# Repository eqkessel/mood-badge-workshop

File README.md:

# mood-badge-workshop
Repository to house my work for making a mood badge for the Spring 2021 Intro to Electronics Pro Milestones Workshop offered through the Purdue Office of Professional Practice.

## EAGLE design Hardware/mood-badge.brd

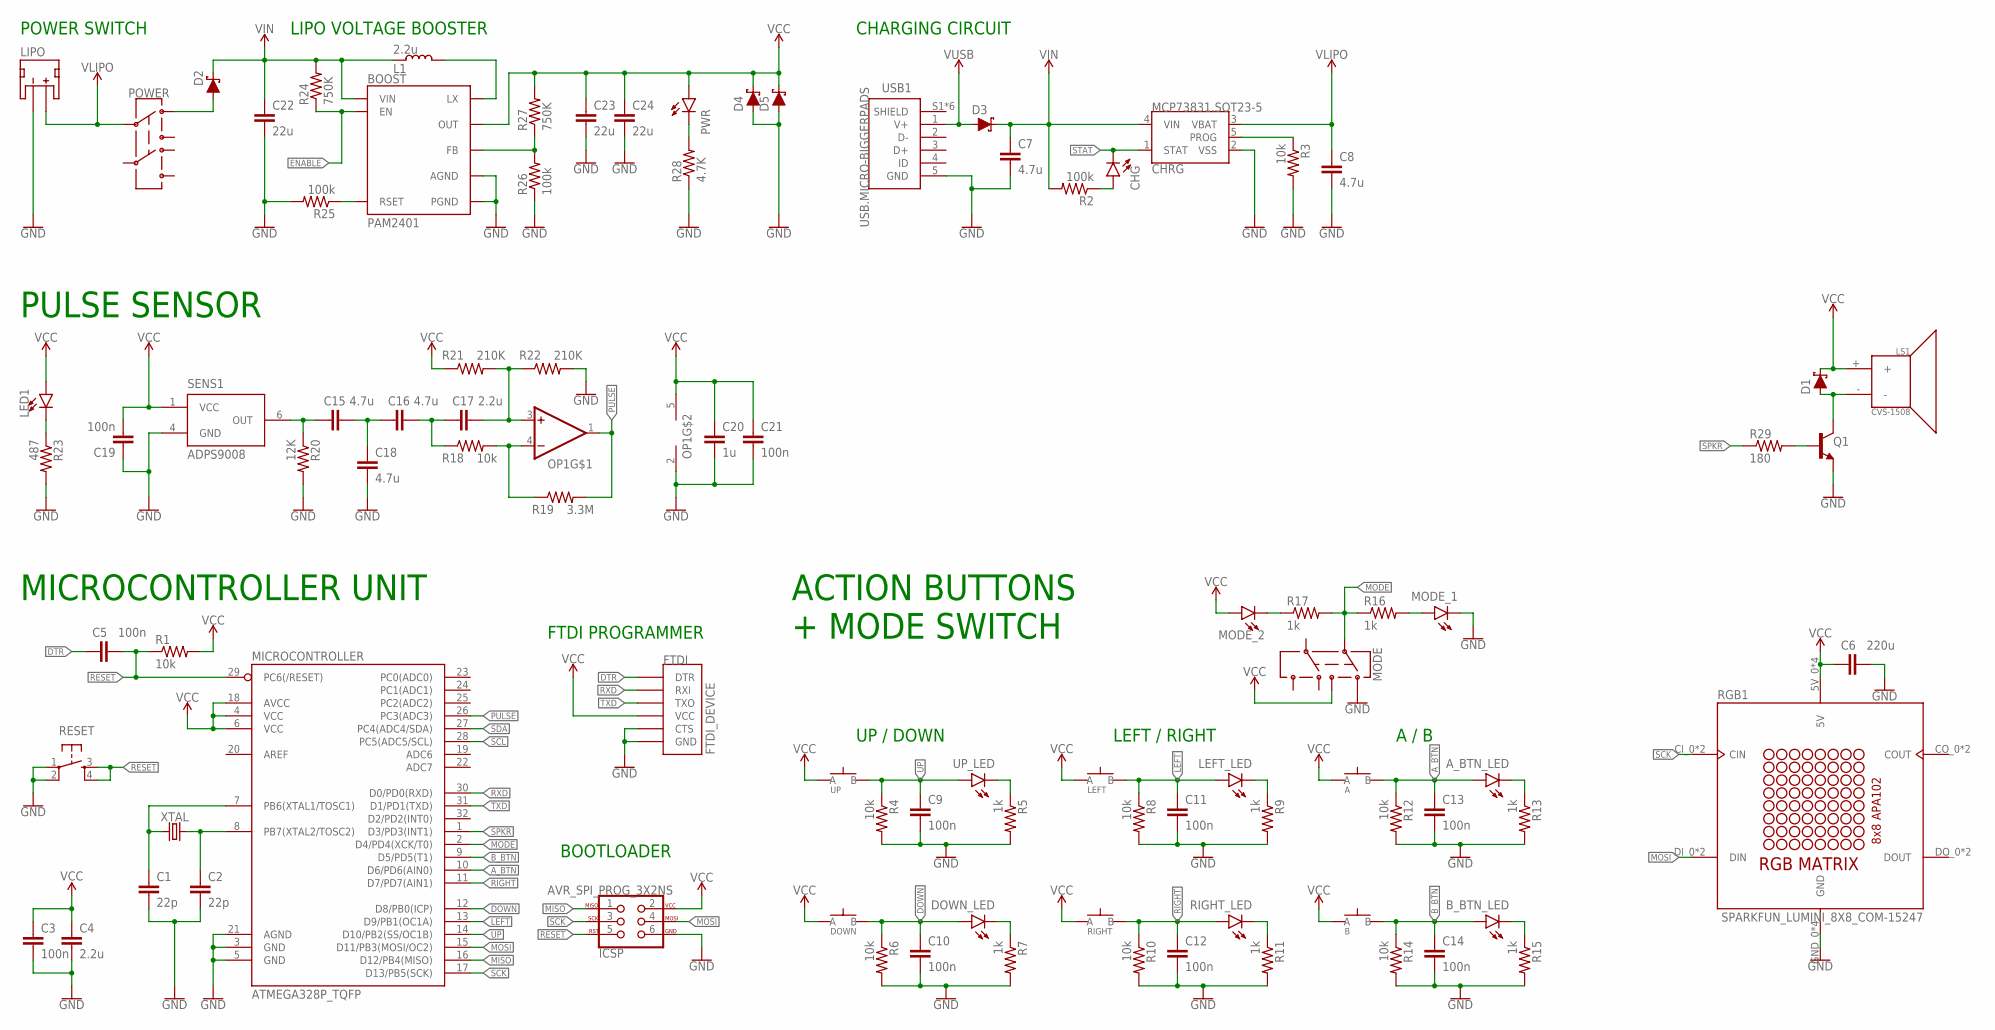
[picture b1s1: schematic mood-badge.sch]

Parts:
A: SPST.KT11P4SM34LFS
A_BTN_LED: LED0603; LED-0603
B: SPST.KT11P4SM34LFS
BOOST: PAM2401; MSOP8
B_BTN_LED: LED0603; LED-0603
C1, C2: 22p; C0603
C3, C5, C9, C10, C11, C12, C13, C14, C19, C21: 100n; C0603
C4, C17: 2.2u; C0603
C6: 220u; C1206
C7, C8, C15, C16, C18: 4.7u; C0603
C20: 1u; C0603
C22, C23, C24: 22u; C0603
CHG: LED0603; LED-0603
CHRG: MCP73831.SOT23-5; SOT23-5
D1, D2, D3, D4, D5: SCHOTTKY-USC; USC
DOWN: SPST.KT11P4SM34LFS
DOWN_LED: LED0603; LED-0603
FTDI: FTDI_DEVICE
ICSP: AVR_SPI_PROG_3X2NS; 2X3-NS
L1: 2.2u; L0603
LED1: LEDZ-BEND; 2-SMD.Z-BEND
LEFT: SPST.KT11P4SM34LFS
LEFT_LED: LED0603; LED-0603
LIPO: JST_2MM_MALE; JST-2-SMD
LS1: CVS-1508; CVS-1508_PCBSPKR
MICROCONTROLLER: ATMEGA328P_TQFP; TQFP32-08
MODE: SWITCH.JS202011JXQNUPWARDS; SWITCH.00
MODE_1, MODE_2: LED0603; LED-0603
OP1: OP-SINGLEOT; SOT23-5
POWER: SWITCH.JS202011JXQNUPWARDS; SWITCH.00
PWR: LED0603; LED-0603
Q1: NPN-GENERIC; SOT23-3
R1, R3, R4, R6, R8, R10, R12, R14, R18: 10k; R0603
R2, R25, R26: 100k; R0603
R5, R7, R9, R11, R13, R15, R16, R17: 1k; R0603
R19: 3.3M; R0603
R20: 12K; R0603
R21, R22: 210K; R0603
R23: 487; R0603
R24, R27: 750K; R0603
R28: 4.7K; R0603
R29: 180; R0603
RESET: SPST-PTS830GG140; BUTTON-GULLWING
RGB1: SPARKFUN_LUMINI_8X8_COM-15247; SPARKFUN_LUMINI_8X8_COM-15047
RIGHT: SPST.KT11P4SM34LFS
RIGHT_LED: LED0603; LED-0603
SENS1: ADPS9008; 6-PIN.CHIPLED
UP: SPST.KT11P4SM34LFS
UP_LED: LED0603; LED-0603
USB1: USB.MICRO-BIGGERPADS; USB-MICRO-01.BIGGERPADS
XTAL: CRYSTAL-CA-310; CA-301

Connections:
A_BTN: A.3 (B), A.4 (B), A_BTN_LED.A, C13.1, MICROCONTROLLER.10 (D6/PD6(AIN0)), R12.1
B_BTN: B.3 (B), B.4 (B), B_BTN_LED.A, C14.1, MICROCONTROLLER.9 (D5/PD5(T1)), R14.1
DOWN: C10.1, DOWN.3 (B), DOWN.4 (B), DOWN_LED.A, MICROCONTROLLER.12 (D8/PB0(ICP)), R6.1
DTR: C5.1, FTDI.DTR
ENABLE: BOOST.2 (EN), R24.1
GND: BOOST.4 (AGND), BOOST.8 (PGND), C1.2, C2.2, C3.2, C4.2, C6.2, C7.2, C8.2, C9.2, C10.2, C11.2, C12.2, C13.2, C14.2, C18.2, C19.1, C20.2, C21.2, C22.2, C23.2, C24.2, CHRG.2 (VSS), D4.+ (A), D5.+ (A), FTDI.CTS, FTDI.GND, ICSP.6, LIPO.1 (-), MICROCONTROLLER.3 (GND), MICROCONTROLLER.5 (GND), MICROCONTROLLER.21 (AGND), MODE.1, MODE_1.C, OP1.2 (V-), Q1.2 (E), R3.2, R4.2, R5.2, R6.2, R7.2, R8.2, R9.2, R10.2, R11.2, R12.2, R13.2, R14.2, R15.2, R20.2, R22.2, R23.2, R25.2, R26.1, R28.1, RESET.1, RESET.2, RGB1.GND_0 (GND), RGB1.GND_1 (GND), RGB1.GND_2 (GND), RGB1.GND_3 (GND), SENS1.4 (GND), USB1.5 (GND)
LEFT: C11.1, LEFT.3 (B), LEFT.4 (B), LEFT_LED.A, MICROCONTROLLER.13 (D9/PB1(OC1A)), R8.1
MISO: ICSP.1, MICROCONTROLLER.16 (D12/PB4(MISO))
MODE: MICROCONTROLLER.2 (D4/PD4(XCK/T0)), MODE.2, R16.1, R17.2
MOSI: ICSP.4, MICROCONTROLLER.15 (D11/PB3(MOSI/OC2)), RGB1.DI_0 (DIN), RGB1.DI_1 (DIN)
unnamed: C1.1, MICROCONTROLLER.7 (PB6(XTAL1/TOSC1)), XTAL.1
unnamed: C2.1, MICROCONTROLLER.8 (PB7(XTAL2/TOSC2)), XTAL.2
unnamed: CHG.A, R2.1
unnamed: D2.+ (A), POWER.1
unnamed: D1.+ (A), LS1.-, Q1.3 (C)
unnamed: CHRG.5 (PROG), R3.1
unnamed: MODE_1.A, R16.2
unnamed: R5.1, UP_LED.C
unnamed: DOWN_LED.C, R7.1
unnamed: LEFT_LED.C, R9.1
unnamed: R11.1, RIGHT_LED.C
unnamed: A_BTN_LED.C, R13.1
unnamed: B_BTN_LED.C, R15.1
unnamed: C15.1, R20.1, SENS1.6 (OUT)
unnamed: MODE_2.C, R17.1
unnamed: C15.2, C16.1, C18.1
unnamed: C16.2, C17.1, R18.1
unnamed: C17.2, OP1.3 (+IN), R21.2, R22.1
unnamed: OP1.4 (-IN), R18.2, R19.1
unnamed: BOOST.6 (RSET), R25.1
unnamed: LED1.- (C), R23.1
unnamed: BOOST.1 (LX), L1.2
unnamed: BOOST.5 (FB), R26.2, R27.1
unnamed: Q1.1 (B), R29.2
unnamed: PWR.C, R28.2
PULSE: MICROCONTROLLER.26 (PC3(ADC3)), OP1.1 (OUT), R19.2
RESET: C5.2, ICSP.5, MICROCONTROLLER.29 (PC6(/RESET)), R1.1, RESET.3, RESET.4
RIGHT: C12.1, MICROCONTROLLER.11 (D7/PD7(AIN1)), R10.1, RIGHT.3 (B), RIGHT.4 (B), RIGHT_LED.A
RXD: FTDI.TXO (RXI), MICROCONTROLLER.30 (D0/PD0(RXD))
SCK: ICSP.3, MICROCONTROLLER.17 (D13/PB5(SCK)), RGB1.CI_0 (CIN), RGB1.CI_1 (CIN)
SCL: MICROCONTROLLER.28 (PC5(ADC5/SCL))
SDA: MICROCONTROLLER.27 (PC4(ADC4/SDA))
SPKR: MICROCONTROLLER.1 (D3/PD3(INT1)), R29.1
STAT: CHG.C, CHRG.1 (STAT)
TXD: FTDI.RXI (TXO), MICROCONTROLLER.31 (D1/PD1(TXD))
UP: C9.1, MICROCONTROLLER.14 (D10/PB2(SS/OC1B)), R4.1, UP.3 (B), UP.4 (B), UP_LED.A
VCC: A.1 (A), A.2 (A), B.1 (A), B.2 (A), BOOST.7 (OUT), C3.1, C4.1, C6.1, C19.2, C20.1, C21.1, C23.1, C24.1, D1.- (C), D4.- (C), D5.- (C), DOWN.1 (A), DOWN.2 (A), FTDI.VCC, ICSP.2, LED1.+ (A), LEFT.1 (A), LEFT.2 (A), LS1.+, MICROCONTROLLER.4 (VCC), MICROCONTROLLER.6 (VCC), MICROCONTROLLER.18 (AVCC), MODE.3, MODE_2.A, OP1.5 (V+), PWR.A, R1.2, R21.1, R27.2, RGB1.5V_0 (5V), RGB1.5V_1 (5V), RGB1.5V_2 (5V), RGB1.5V_3 (5V), RIGHT.1 (A), RIGHT.2 (A), SENS1.1 (VCC), UP.1 (A), UP.2 (A)
VIN: BOOST.3 (VIN), C7.1, C22.1, CHRG.4 (VIN), D2.- (C), D3.- (C), L1.1, R2.2, R24.2
VLIPO: C8.1, CHRG.3 (VBAT), LIPO.2 (+), POWER.2
V_USB: D3.+ (A), USB1.1 (V+)

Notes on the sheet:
BOOTLOADER
FTDI PROGRAMMER
MICROCONTROLLER UNIT
POWER SWITCH
CHARGING CIRCUIT
ACTION BUTTONS + MODE SWITCH
UP / DOWN
LEFT / RIGHT
A / B
LIPO VOLTAGE BOOSTER
PULSE SENSOR

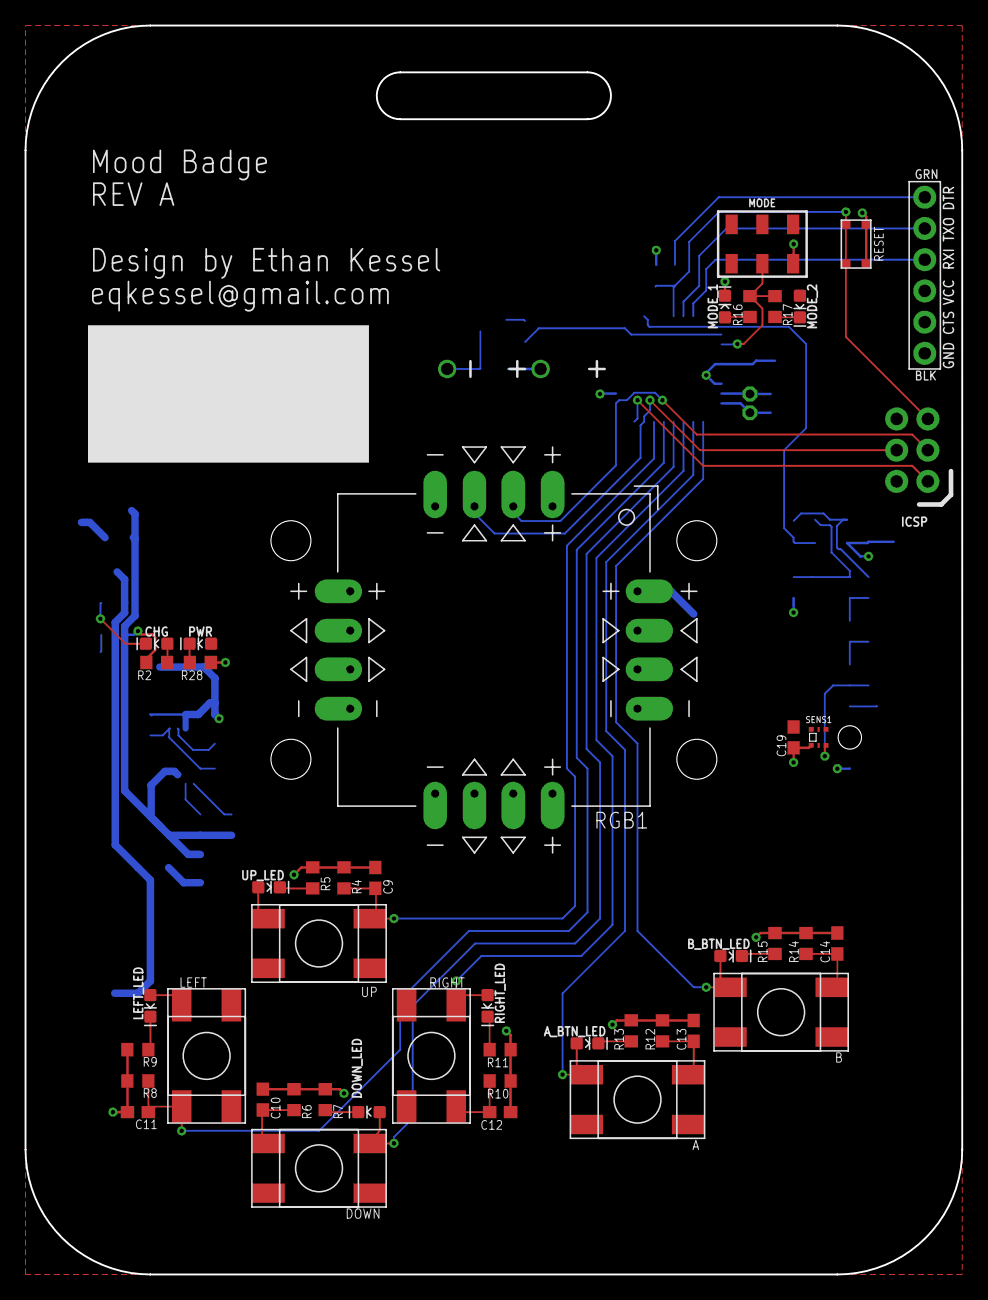
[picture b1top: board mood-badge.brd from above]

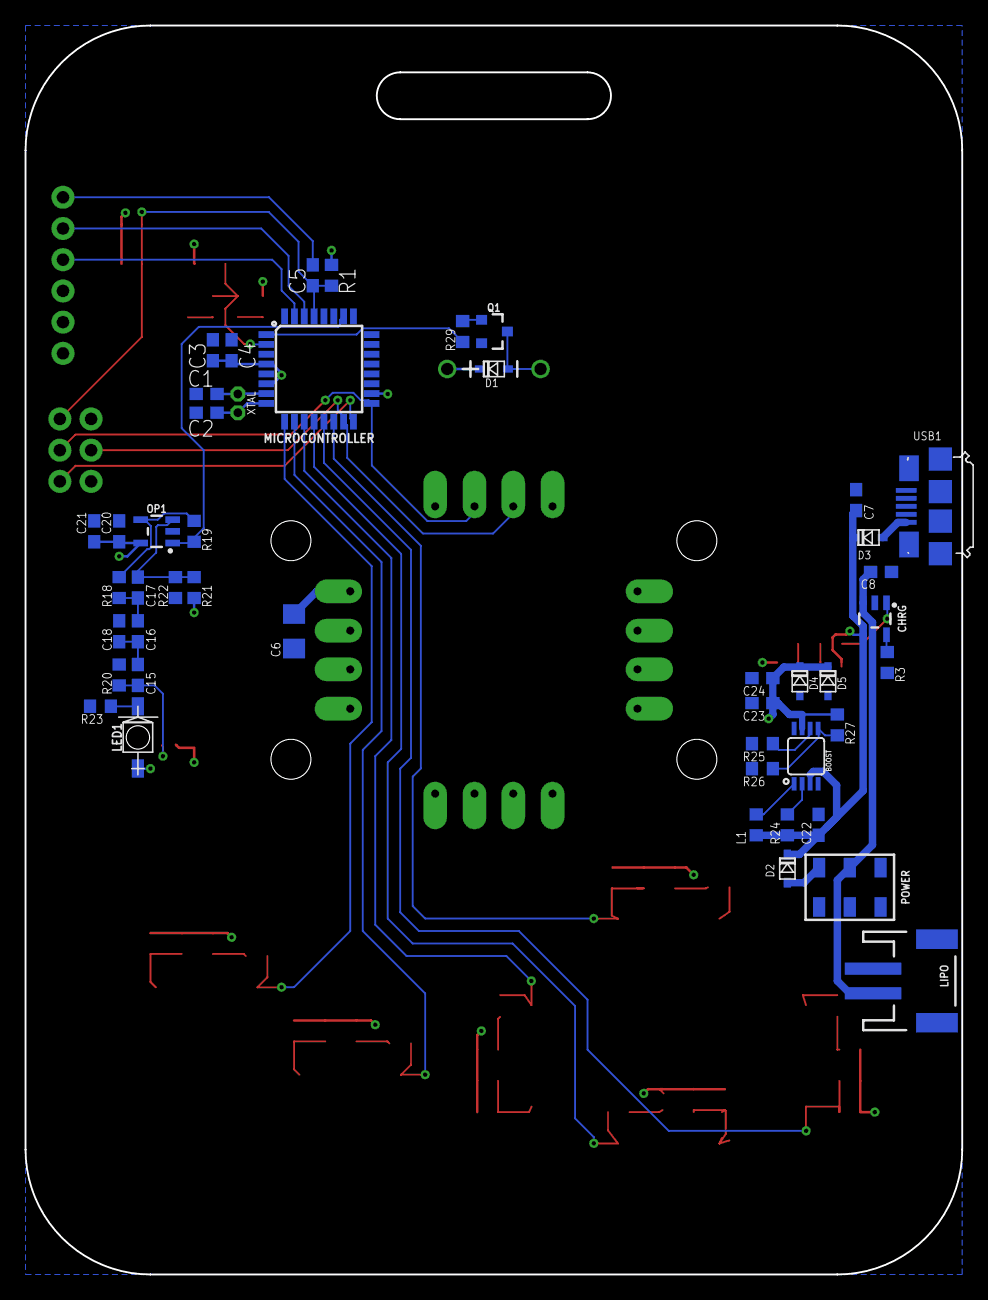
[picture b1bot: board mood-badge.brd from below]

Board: 2 copper layers, 76.2 x 101.6 mm, 92 parts (46 on the bottom side), 48 nets.

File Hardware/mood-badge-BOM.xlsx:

Mood Badge -- REV A / Ethan Kessel |  |  |  |  |  |  |  |  |  |  | Total | 43.839999999999996 | Total (in Bulk) | 0
BOM # | Comment | Designator | Description | Mounting Type | Package | Manufacturer | Manufacturer PN | Supplier | Supplier PN | Price per unit | Quantity | Total | Per 100 | Total
1 | ATmega328 | MICROCONTROLLER | AVR AVR® ATmega Microcontroller IC 8-Bit 20MHz 32KB (16K x 16) FLASH 32-TQFP (7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 | SMD | 32-TQFP (7x7) | Microchip Technology | ATMEGA328P-AUR | Digi-Key | ATMEGA328P-AURCT-ND | 2.14 | 1 | 2.14
2 | 8MHz Crystal | XTAL | 8MHz ±30ppm Crystal 18pF 80 Ohm -20°C ~ 70°C Through Hole Cylindrical Can, Radi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 | THT | Cylindrical Can, Radial | EPSON | CA-301 8.0000M-C:PBFREE | Digi-Key | SER3414-ND | 0.83 | 1 | 0.83
3 | Right Angle, 6Pos Male Headers | FTDI | 40 Positions Header, Breakaway Connector 0.100" (2.54mm) Through Hole, Right An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 | THT |  | Sullins Connector Solutions | PRPC040SBAN-M71RC | Digi-Key | S1111EC-40-ND | 0.14000000000000001 | 1 | 0.14000000000000001
4 | 2x3 Male Pin Headers |  | Connector Header Through Hole 6 position 0.100" (2.54mm) | THT |  | Adam Tech | PH2-06-UA | Digi-Key | 2057-PH2-06-UA-ND | 0.12 | 1 | 0.12
5 | Tiny Rectangular Button | RESET | Tactile Switch SPST-NO Top Actuated Surface Mount | SMD | Gull Wing | C&K Components | PTS830GM140 SMTR LFS | Digi-Key | CKN10587CT-ND | 0.56000000000000005 | 1 | 0.56000000000000005
6 | Square Button | LEFT, RIGHT, UP, DOWN, A_BTN, B_BTN | Tactile Switch SPST-NO Top Actuated Surface Mount | SMD | Gull Wing | C&K | PTS645SM43SMTR92 LFS | Digi-Key | CKN9112CT-ND | 0.15 | 5 | 0.75
7 | Switch | POWER,MODE | SWITCH SLIDE DPDT 300MA 6V | SMD | J Lead | C&K | JS202011JCQN | Digi-Key | CKN10723CT-ND | 0.48 | 2 | 0.96
8 | Speaker | LS1 | Mini Speaker - PC Mount 12mm 2.048kHz | THT |  | CUI Inc. | CEM-1203(42) | Sparkfun Electronics | COM-07950 | 1.95 | 1 | 1.95
9 | Micro USB | USB1 | USB - micro B USB 2.0 Receptacle Connector 5 Position Surface Mount, Right Angle | SMD | Flange, Horizontal | Amphenol FCI | 10118192-0001LF | Digi-Key | 609-4613-1-ND | 0.43 | 1 | 0.43
10 | JST Connector | LIPO | JST Right Angle Connector - White | SMD | NA | 4UCOM Technology Inc. |  | Sparkfun Electronics | PRT-08612 | 0.95 | 1 | 0.95
11 | MCP73831 T Li-Ion, Li-Pol Controller | CHRG | Charger IC Lithium-Ion/Polymer SOT-23-5 | SMD | SOT-23-5 | Microchip Technology | MCP73831T-2ACI/OT | Digi-Key | MCP73831T-2ACI/OTCT-ND | 0.56000000000000005 | 1 | 0.56000000000000005
12 | PAM2401 Boost Converter | BOOST | Boost Switching Regulator IC Positive Adjustable 2.5V 1 Output 1A 8-TSSOP, 8-MS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 | SMD | 8-MSOP | Diodes Incorporated | PAM2401SCADJ | Digi-Key | PAM2401SCADJDICT-ND | 1.05 | 1 | 1.05
13 | RGB LED Matrix | RGB1 | SparkFun LuMini LED Matrix | Custom | PCB | SparkFun Electronics | COM-15047 | Digi-Key | 1568-COM-15047-ND | 25.95 | 1 | 25.95
14 | MCP6001 | OP1 | General Purpose Amplifier 1 Circuit Rail-to-Rail SOT-23-5 | SMD | SOT-23-5 | Microchip Technology | MCP6001T-E/OTCT-ND | Digi-Key | MCP6001T-E/OTCT-ND | 0.28999999999999998 | 1 | 0.28999999999999998
15 | APDS-9008 | SENS | Optical Sensor Ambient 565nm Current 6-SMD, No Lead | SMD | 6-SMD, No Lead | Broadcom Limited | APDS-9008-020 | Digi-Key | 516-2662-1-ND | 1.04 | 1 | 1.04
16 | NPN Transistor | Q1 | Bipolar (BJT) Transistor NPN 40V 600mA 300MHz 250mW Surface Mount TO-236AB | SMD | TO-236AB | Nexperia USA Inc. | PMBT2222A,215 | Digi-Key | 1727-2956-1-ND | 1.05 | 1 | 1.05
17 | Schottky Diode | D1, D2, D3, D4, D5 | Diode Schottky 30V 1.5A Surface Mount USC | SMD | USC | Toshiba Semiconductor and Storage | CUS15S30,H3F | Digi-Key | CUS15S30H3FCT-ND | 0.26 | 5 | 1.3
18 | Green LED | UP_LED, DOWN_LED, LEFT_LED, RIGHT_LED, A_BTN_LED, B_BTN_LED, MODE_1, MODE_2, PW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 | Green 571 nm, 2 V | SMD | 0603 | Lite-On Inc | LTST-C190KGKT | Digi-Key | 160-1435-1-ND | 0.27 | 10 | 2.7
19 | 2.2u Inductor | L1 |  | SMD | 0603 |  |  |  |  |  | 1 | 0
20 | 10k Resistor | R1, R3, R4, R6, R8, R10, R12, R14, R18 | 10 kOhms ±1% 0.1W, 1/10W Chip Resistor 0603 (1608 Metric) Automotive AEC-Q200 T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 | SMD | 0603 | Stackpole Electronics Inc | RMCF0603FT10K0 | Digi-Key | RMCF0603FT10K0CT-ND | 0.01 | 9 | 0.09
21 | 100k Resistor | R2, R25, R26 | 100 kOhms ±1% 0.1W, 1/10W Chip Resistor 0603 (1608 Metric) Automotive AEC-Q200 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 | SMD | 0603 | Stackpole Electronics Inc | RMCF0603FT100K | Digi-Key | RMCF0603FT100KCT-ND | 0.01 | 3 | 0.03
22 | 1k Resistor | R5, R7, R9, R11, R13, R15, R16, R17 | 1 kOhms ±1% 0.1W, 1/10W Chip Resistor 0603 (1608 Metric) Automotive AEC-Q200 Th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 | SMD | 0603 | Stackpole Electronics Inc | RMCF0603FT1K00 | Digi-Key | RMCF0603FT1K00CT-ND | 0.01 | 8 | 0.08
23 | 210k Resistor | R21, R22 |  | SMD | 0603 |  |  |  |  |  | 2 | 0
24 | 750k Resistor | R24, R27 |  | SMD | 0603 |  |  |  |  |  | 2 | 0
25 | 487 Resistor | R23 |  | SMD | 0603 |  |  |  |  |  | 1 | 0
26 | 180 Resistor | R29 |  | SMD | 0603 |  |  |  |  |  | 1 | 0
27 | 12k Resistor | R20 |  | SMD | 0603 |  |  |  |  |  | 1 | 0
28 | 4.7k Resistor | R28 | 4.7 kOhms ±1% 0.1W, 1/10W Chip Resistor 0603 (1608 Metric) Automotive AEC-Q200 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 | SMD | 0603 | Stackpole Electronics Inc | RMCF0603FT4K70 | Digi-Key | RMCF0603FT4K70CT-ND | 0.01
29 | 3.3M Resistor | R19 |  | SMD | 0603 |  |  |  |  |  | 1 | 0
30 | 100n Capacitor | C3, C5, C9, C10, C11, C12, C13, C14, C19, C21 | 0.1µF ±5% 16V Ceramic Capacitor X7R 0603 (1608 Metric) | SMD | 0603 | Yageo | CC0603JRX7R7BB104 | Digi-Key | 311-1776-1-ND | 0.03 | 10 | 0.3
31 | 4.7u Capacitor | C7, C8, C15, C16, C18 |  | SMD | 0603 |  |  |  |  |  | 5 | 0
32 | 22u Capacitor | C22, C23, C24 | 22µF ±20% 10V Ceramic Capacitor X5R 0603 (1608 Metric) | SMD | 0603 | Samsung Electro-Mechanics | CL10A226MP8NUNE | Digi-Key | 1276-1274-1-ND | 7.0000000000000007E-2 | 3 | 0.21000000000000002
33 | 22p Capacitor | C1, C2 |  | SMD | 0603 |  |  |  |  |  | 2 | 0
34 | 2.2u Capacitor | C4, C17 | 2.2µF ±10% 16V Ceramic Capacitor X5R 0603 (1608 Metric) | SMD | 0603 | Murata Electronics North America | GRM188R61C225KE15D | Digi-Key | 490-3296-1-ND | 0.13 | 2 | 0.26
35 | 1u Capacitor | C20 | 1µF ±10% 25V Ceramic Capacitor X5R 0603 (1608 Metric) | SMD | 0603 | Samsung Electro-Mechanics | CL10A105KA8NNNC | Digi-Key | 1276-1102-1-ND | 0.1 | 1 | 0.1
36 | 220u Capacitor | C6 |  | SMD | 1206 |  |  |  |  |  | 1 | 0

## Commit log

2021-02-20 Step 06 Init Repo Required Word File
    Making a commit to master reeeeeeeeeeeeeee
2021-02-20 Tweaks to autogenerated .gitignore to add missing items from template
2021-02-20 Commit empty schematic and board files
2021-02-20 Add mood-badge-BOM.xlsx spreadsheet
2021-02-20 Updated word doc to include rudimentary specs
2021-02-20 Sketch of design
2021-02-20 Requested corrections to .gitignore file
2021-02-27 Downscale image
2021-02-27 PCB perimeter imported from Fusion 360 sketch
    Will include Fusion 360 file later
2021-03-06 Added microcontroller unit and started on power supply design
2021-03-10 Finished charger circuit and added action buttons
2021-03-13 Pulse sensor and LiPo voltage booster to use 5v logic
2021-03-13 .gitignore update to ignore library file autosaves
2021-03-13 Adafruit 8x8 Dotstar Matrix Part
2021-03-14 PCB layout work
2021-03-17 Adjustments to PCB trace widths and connections to buttons added
2021-03-19 PCB Routed
2021-03-20 Swap out matrix for different part with better connector layout
2021-03-25 Name/contact/revision on PCB
2021-03-27 Minor fixes and routing changes
2021-03-27 Updated BOM, minor tweaks to part values
2021-03-27 Fixed diode numbering
2021-04-03 Found parts for missing passives and added LiPo Battery

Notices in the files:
parts and their libraries:
SparkFun-IC-Power: Licensing: Creative Commons ShareAlike 4.0 International - https://creativecommons.org/licenses/by-sa/4.0
